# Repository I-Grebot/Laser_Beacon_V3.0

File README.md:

# Laser_Beacon_V3.0
IGrebot's current Beacons system aiming at opponent detection and absolute positioning.

See more on : http://wiki.igrebot.fr/index.php?title=Beacon_V3.0

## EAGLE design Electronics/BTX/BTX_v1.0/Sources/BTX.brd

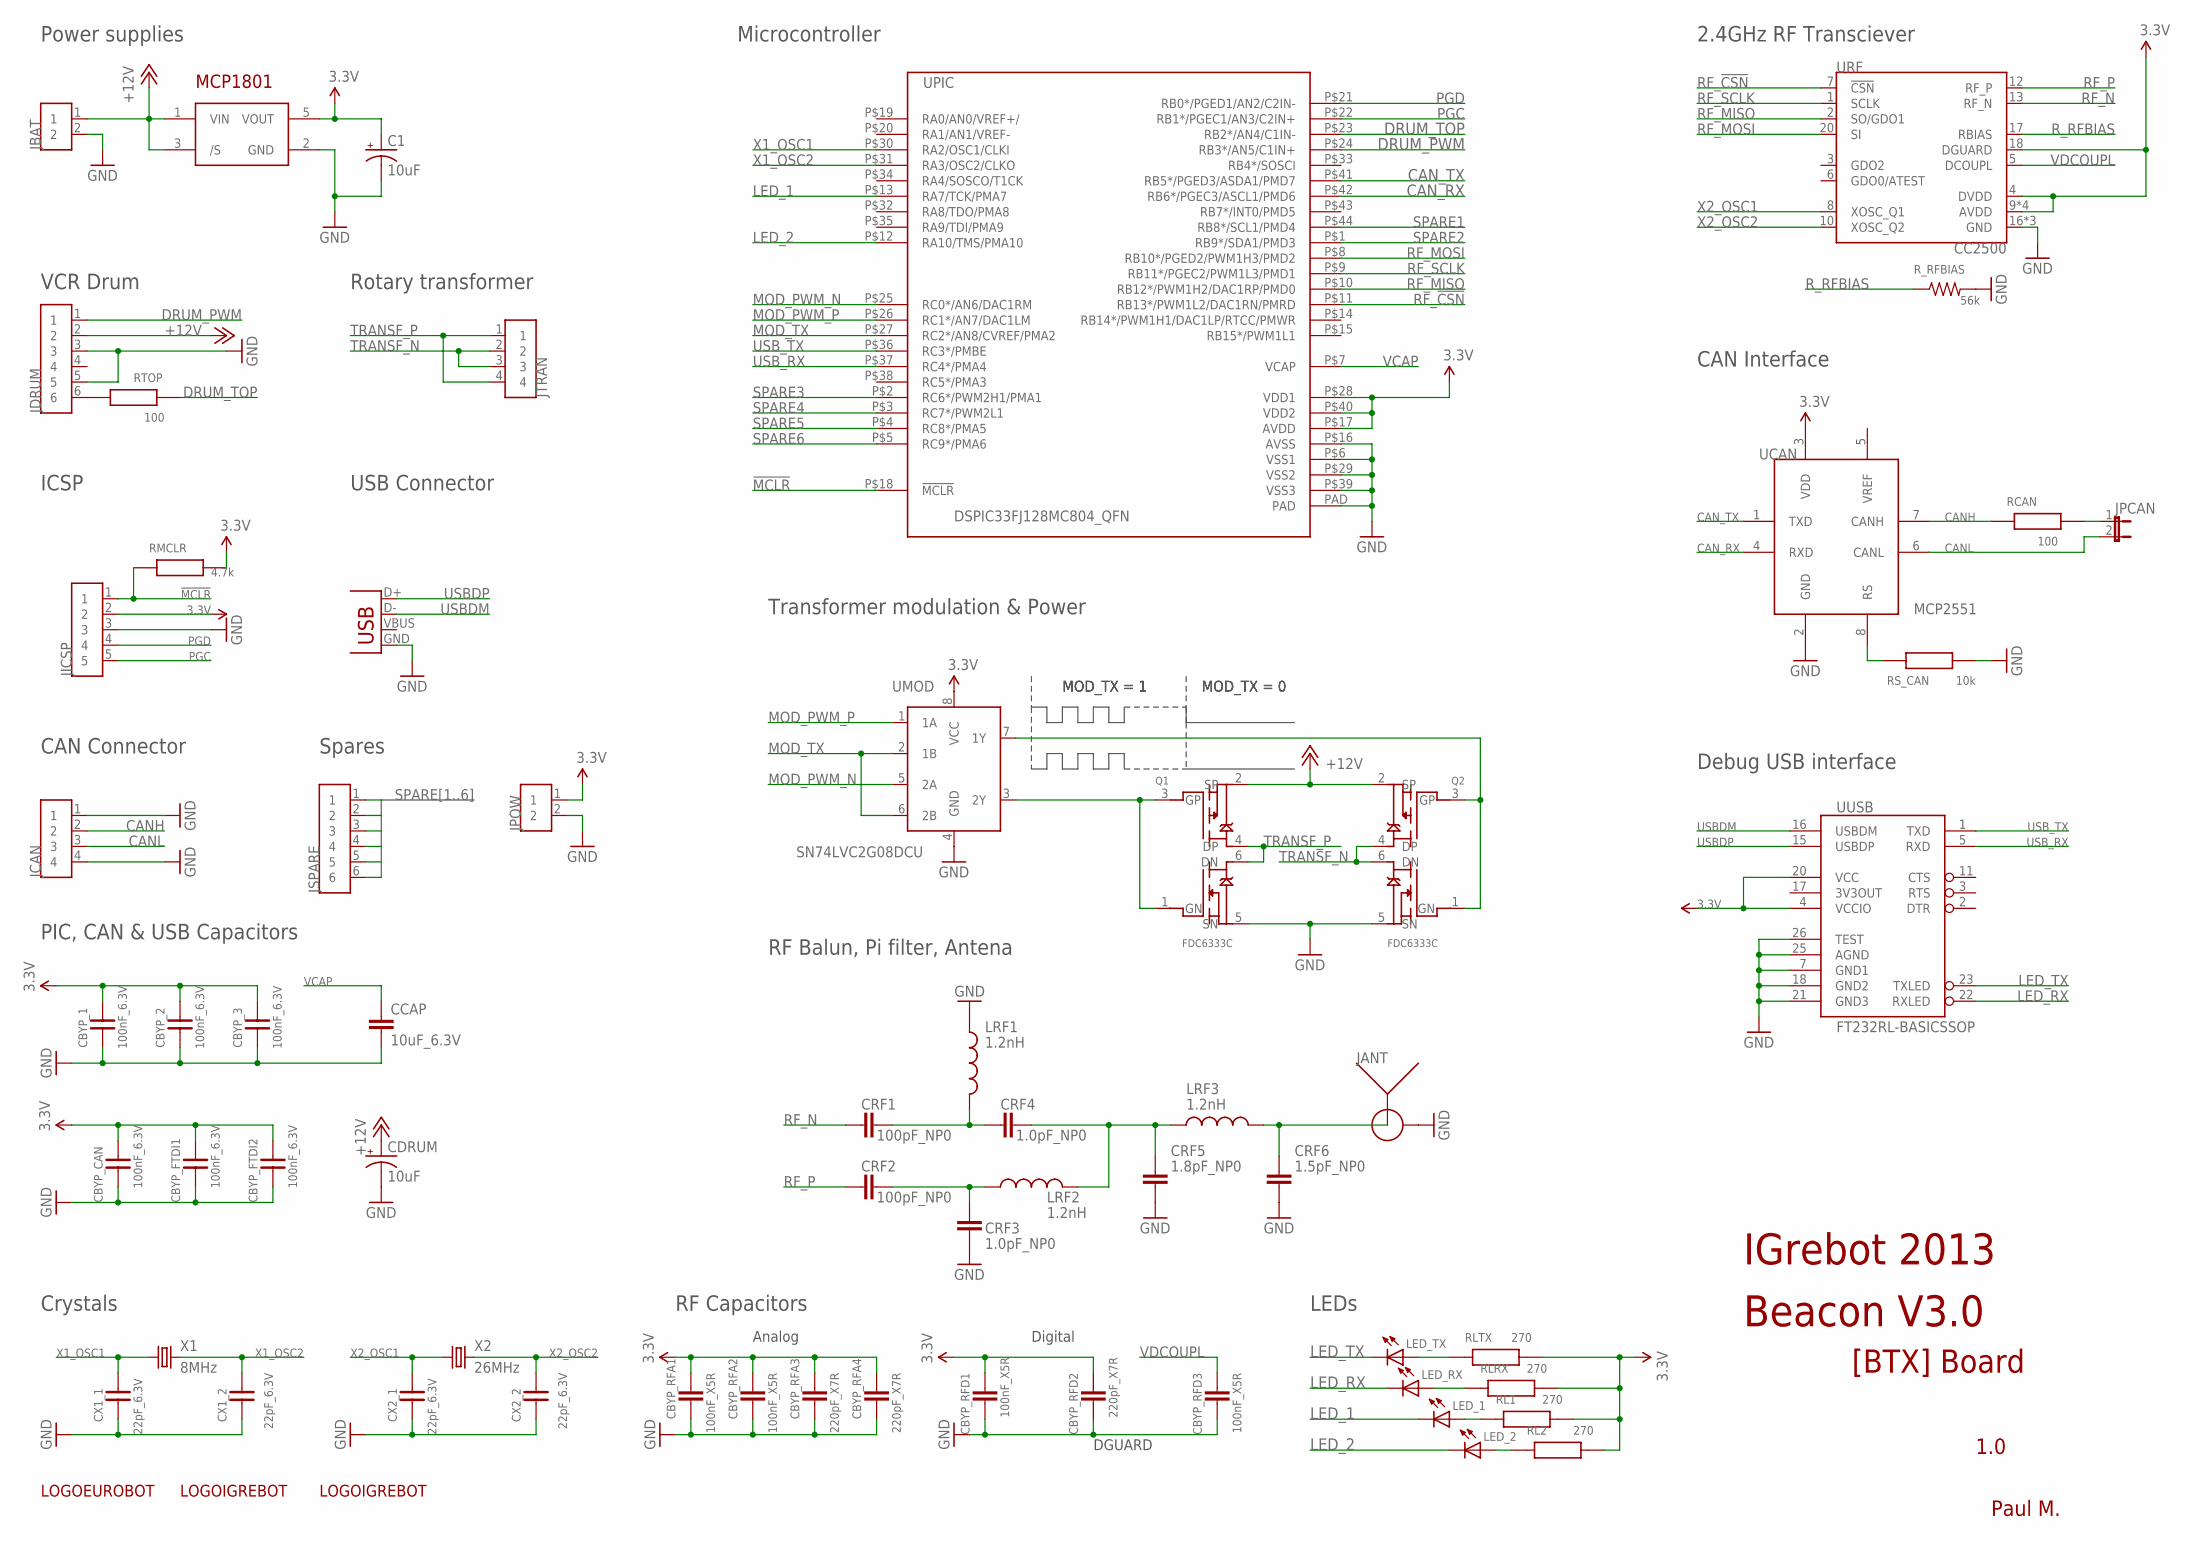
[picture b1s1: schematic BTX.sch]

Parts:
C1: 10uF; PANASONIC_C
CBYP_1, CBYP_2, CBYP_3: 100nF_6.3V; R0603
CBYP_CAN: 100nF_6.3V; R0603
CBYP_FTDI1, CBYP_FTDI2: 100nF_6.3V; R0603
CBYP_RFA1, CBYP_RFA2: 100nF_X5R; 0402-CAP
CBYP_RFA3, CBYP_RFA4: 220pF_X7R; 0402-CAP
CBYP_RFD1, CBYP_RFD3: 100nF_X5R; 0402-CAP
CBYP_RFD2: 220pF_X7R; 0402-CAP
CCAP: 10uF_6.3V; 1206
CDRUM: 10uF; PANASONIC_C
CRF1, CRF2: 100pF_NP0; 0402-CAP
CRF3, CRF4: 1.0pF_NP0; 0402-CAP
CRF5: 1.8pF_NP0; 0402-CAP
CRF6: 1.5pF_NP0; 0402-CAP
CX1_1, CX1_2, CX2_1, CX2_2: 22pF_6.3V; R0603
JANT: ENG_CD_1814400_C1; SMA-PCB-ANGLE
JBAT: MULTICOMP_PA001-2; CON2-5.00
JCAN: SIL4; CON4-2.54
JDRUM: SIL6; CON6-2.54
JICSP: SIL5; CON5-2.54
JPCAN: JUMPER-2PTH_LOCK; 1X02_LOCK
JPOW: SIL2; CON2-2.54
JSPARE: SIL6; CON6-2.54
JTRAN: SIL4; CON4-2.54
JUSB: USBSMD; USB-MINIB
LED_1, LED_2: LED0603; LED-0603
LED_RX: LED0603; LED-0603
LED_TX: LED0603; LED-0603
LRF1, LRF2, LRF3: 1.2nH; C0402
Q1, Q2: FDC6333C; SSOT6
RCAN: 100; R0603
RL1, RL2: 270; R0603
RLRX: 270; R0603
RLTX: 270; R0603
RMCLR: 4.7k; R0603
RS_CAN: 10k; R0603
RTOP: 100; R0603
R_RFBIAS: 56k; 0402-RES
U$3: LOGOEUROBOT; LOGO_EUROBOT_1
U$5, U$9: LOGOIGREBOT; LOGO_IGREBOT
UCAN: MCP2551; SO-08
UMOD: SN74LVC2G08DCU; DCU8
UPIC: DSPIC33FJ128MC804_QFN; QFN44-8X8
UREG: MCP1801; SOT23-5L
URF: CC2500; QFN20-0.5
UUSB: FT232RL-BASICSSOP; SSOP28DB
X1: 8MHz; XTAL_4.9-1.8
X2: 26MHz; XTAL_4.9-1.8

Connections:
3.3V: C1.+, CBYP_1.1, CBYP_2.1, CBYP_3.1, CBYP_CAN.1, CBYP_FTDI1.1, CBYP_FTDI2.1, CBYP_RFA1.2, CBYP_RFA2.2, CBYP_RFA3.2, CBYP_RFA4.2, CBYP_RFD1.2, CBYP_RFD2.2, JICSP.2, JPOW.1, RL1.1, RL2.1, RLRX.1, RLTX.1, RMCLR.1, UCAN.3 (VDD), UMOD.8 (VCC), UPIC.P$17 (AVDD), UPIC.P$28 (VDD1), UPIC.P$40 (VDD2), UREG.5 (VOUT), URF.4 (DVDD), URF.9 (AVDD), URF.11 (AVDD), URF.14 (AVDD), URF.15 (AVDD), URF.18 (DGUARD), UUSB.4 (VCCIO), UUSB.20 (VCC)
!MCLR!: JICSP.1, RMCLR.2, UPIC.P$18 (!MCLR)
+12V: CDRUM.+, JBAT.1, JDRUM.2, Q1.2 (SP), Q2.2 (SP), UREG.1 (VIN), UREG.3 (/S)
CANH: JCAN.2, RCAN.1, UCAN.7 (CANH)
CANL: JCAN.3, JPCAN.2, UCAN.6 (CANL)
CAN_RX: UCAN.4 (RXD), UPIC.P$42 (RB6*/PGEC3/ASCL1/PMD6)
CAN_TX: UCAN.1 (TXD), UPIC.P$41 (RB5*/PGED3/ASDA1/PMD7)
DRUM_PWM: JDRUM.1, UPIC.P$24 (RB3*/AN5/C1IN+)
DRUM_TOP: RTOP.1, UPIC.P$23 (RB2*/AN4/C1IN-)
GND: C1.-, CBYP_1.2, CBYP_2.2, CBYP_3.2, CBYP_CAN.2, CBYP_FTDI1.2, CBYP_FTDI2.2, CBYP_RFA1.1, CBYP_RFA2.1, CBYP_RFA3.1, CBYP_RFA4.1, CBYP_RFD1.1, CBYP_RFD2.1, CBYP_RFD3.1, CCAP.2, CDRUM.-, CRF3.1, CRF5.1, CRF6.1, CX1_1.2, CX1_2.2, CX2_1.2, CX2_2.2, JANT.B1 (B), JANT.B2 (B), JANT.B3 (B), JANT.B4 (B), JBAT.2, JCAN.1, JCAN.4, JDRUM.3, JDRUM.5, JICSP.3, JPOW.2, JUSB.GND, LRF1.1, Q1.5 (SN), Q2.5 (SN), RS_CAN.1, R_RFBIAS.2, UCAN.2 (GND), UMOD.4 (GND), UPIC.P$6 (VSS1), UPIC.P$16 (AVSS), UPIC.P$29 (VSS2), UPIC.P$39 (VSS3), UPIC.PAD, UREG.2 (GND), URF.16 (GND), URF.19 (GND), URF.PAD (GND), UUSB.7 (GND1), UUSB.18 (GND2), UUSB.21 (GND3), UUSB.25 (AGND), UUSB.26 (TEST)
LED_1: LED_1.C, UPIC.P$13 (RA7/TCK/PMA7)
LED_2: LED_2.C, UPIC.P$12 (RA10/TMS/PMA10)
LED_RX: LED_RX.C, UUSB.22 (RXLED)
LED_TX: LED_TX.C, UUSB.23 (TXLED)
MOD_N: Q1.1 (GN), Q1.3 (GP), UMOD.3 (2Y)
MOD_P: Q2.1 (GN), Q2.3 (GP), UMOD.7 (1Y)
MOD_PWM_N: UMOD.5 (2A), UPIC.P$25 (RC0*/AN6/DAC1RM)
MOD_PWM_P: UMOD.1 (1A), UPIC.P$26 (RC1*/AN7/DAC1LM)
MOD_TX: UMOD.2 (1B), UMOD.6 (2B), UPIC.P$27 (RC2*/AN8/CVREF/PMA2)
unnamed: CRF1.2, CRF4.2, LRF1.2
unnamed: LED_TX.A, RLTX.2
unnamed: CRF2.2, CRF3.2, LRF2.1
unnamed: CRF4.1, CRF5.2, LRF2.2, LRF3.1
unnamed: RS_CAN.2, UCAN.8 (RS)
unnamed: JPCAN.1, RCAN.2
unnamed: CRF6.2, JANT.A, LRF3.2
unnamed: LED_RX.A, RLRX.2
unnamed: LED_1.A, RL1.2
unnamed: LED_2.A, RL2.2
PGC: JICSP.5, UPIC.P$22 (RB1*/PGEC1/AN3/C2IN+)
PGD: JICSP.4, UPIC.P$21 (RB0*/PGED1/AN2/C2IN-)
RF_!CSN!: UPIC.P$11 (RB13*/PWM1L2/DAC1RN/PMRD), URF.7 (!CSN!)
RF_MISO: UPIC.P$10 (RB12*/PWM1H2/DAC1RP/PMD0), URF.2 (SO/GDO1)
RF_MOSI: UPIC.P$8 (RB10*/PGED2/PWM1H3/PMD2), URF.20 (SI)
RF_N: CRF1.1, URF.13 (RF_N)
RF_P: CRF2.1, URF.12 (RF_P)
RF_SCLK: UPIC.P$9 (RB11*/PGEC2/PWM1L3/PMD1), URF.1 (SCLK)
RTOP: JDRUM.6, RTOP.2
R_RFBIAS: R_RFBIAS.1, URF.17 (RBIAS)
SPARE1: JSPARE.1, UPIC.P$44 (RB8*/SCL1/PMD4)
SPARE2: JSPARE.2, UPIC.P$1 (RB9*/SDA1/PMD3)
SPARE3: JSPARE.3, UPIC.P$2 (RC6*/PWM2H1/PMA1)
SPARE4: JSPARE.4, UPIC.P$3 (RC7*/PWM2L1)
SPARE5: JSPARE.5, UPIC.P$4 (RC8*/PMA5)
SPARE6: JSPARE.6, UPIC.P$5 (RC9*/PMA6)
TRANSF_N: JTRAN.2, JTRAN.3, Q2.4 (DP), Q2.6 (DN)
TRANSF_P: JTRAN.1, JTRAN.4, Q1.4 (DP), Q1.6 (DN)
USBDM: JUSB.D-, UUSB.16 (USBDM)
USBDP: JUSB.D+, UUSB.15 (USBDP)
USB_RX: UPIC.P$37 (RC4*/PMA4), UUSB.5 (RXD)
USB_TX: UPIC.P$36 (RC3*/PMBE), UUSB.1 (TXD)
VCAP: CCAP.1, UPIC.P$7 (VCAP)
VDCOUPL: CBYP_RFD3.2, URF.5 (DCOUPL)
X1_OSC1: CX1_1.1, UPIC.P$30 (RA2/OSC1/CLKI), X1.P$1 (1)
X1_OSC2: CX1_2.1, UPIC.P$31 (RA3/OSC2/CLKO), X1.P$2 (2)
X2_OSC1: CX2_1.1, URF.8 (XOSC_Q1), X2.P$1 (1)
X2_OSC2: CX2_2.1, URF.10 (XOSC_Q2), X2.P$2 (2)

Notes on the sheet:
Debug USB interface
CAN Interface
LEDs
PIC, CAN & USB Capacitors
USB Connector
Power supplies
ICSP
Rotary transformer
VCR Drum
Transformer modulation & Power
DGUARD
RF Balun, Pi filter, Antena
2.4GHz RF Transciever
Crystals
RF Capacitors
Analog
Digital
CAN Connector
Microcontroller
MOD_TX = 1
MOD_TX = 0
Spares
IGrebot 2013
Beacon V3.0
[BTX] Board
1.0
Paul M.

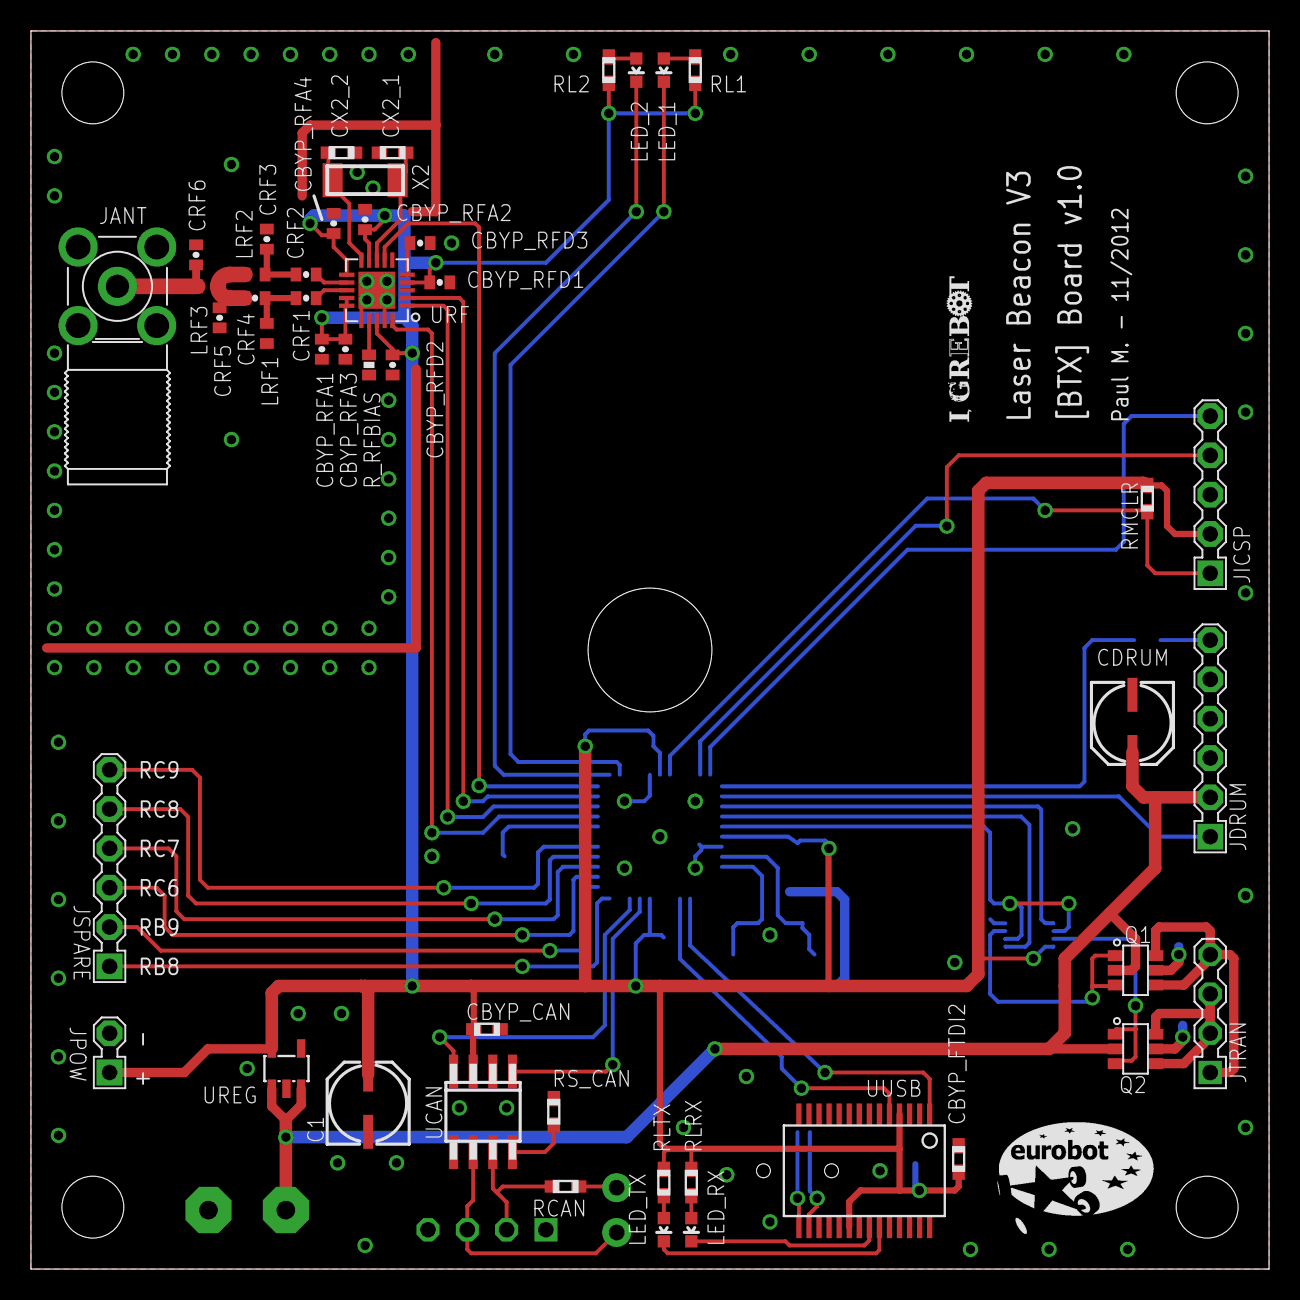
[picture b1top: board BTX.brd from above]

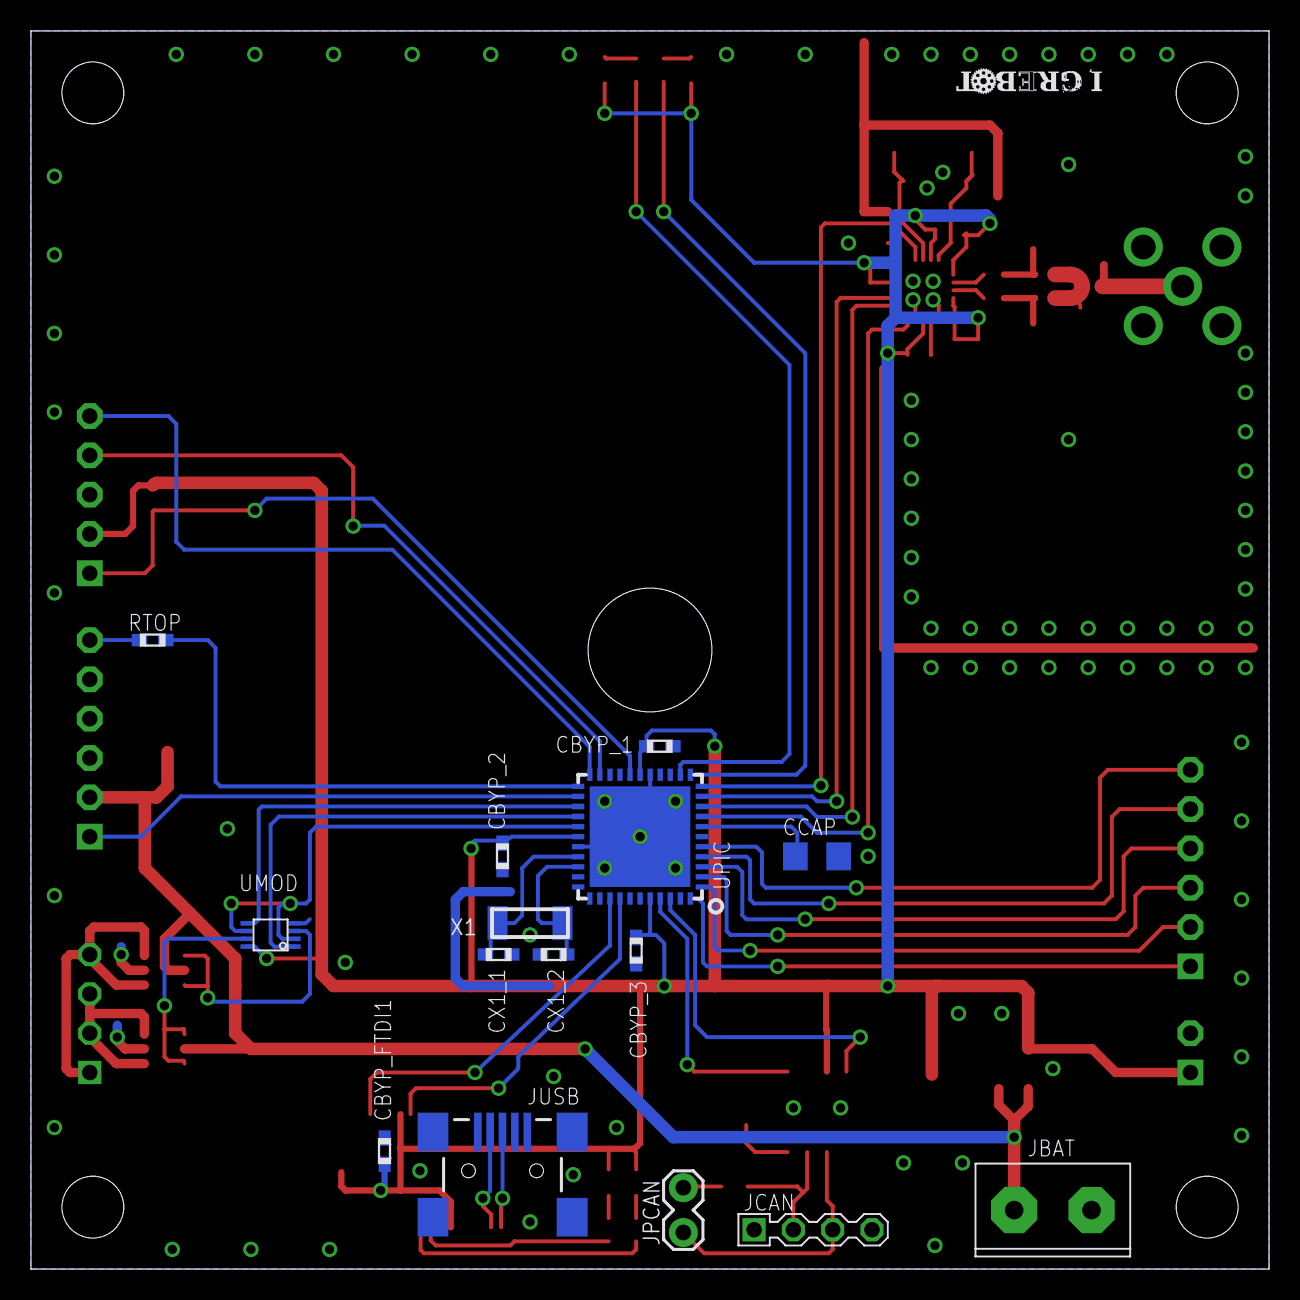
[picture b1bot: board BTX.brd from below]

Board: 2 copper layers, 80.0 x 80.0 mm, 65 parts (16 on the bottom side), 57 nets.

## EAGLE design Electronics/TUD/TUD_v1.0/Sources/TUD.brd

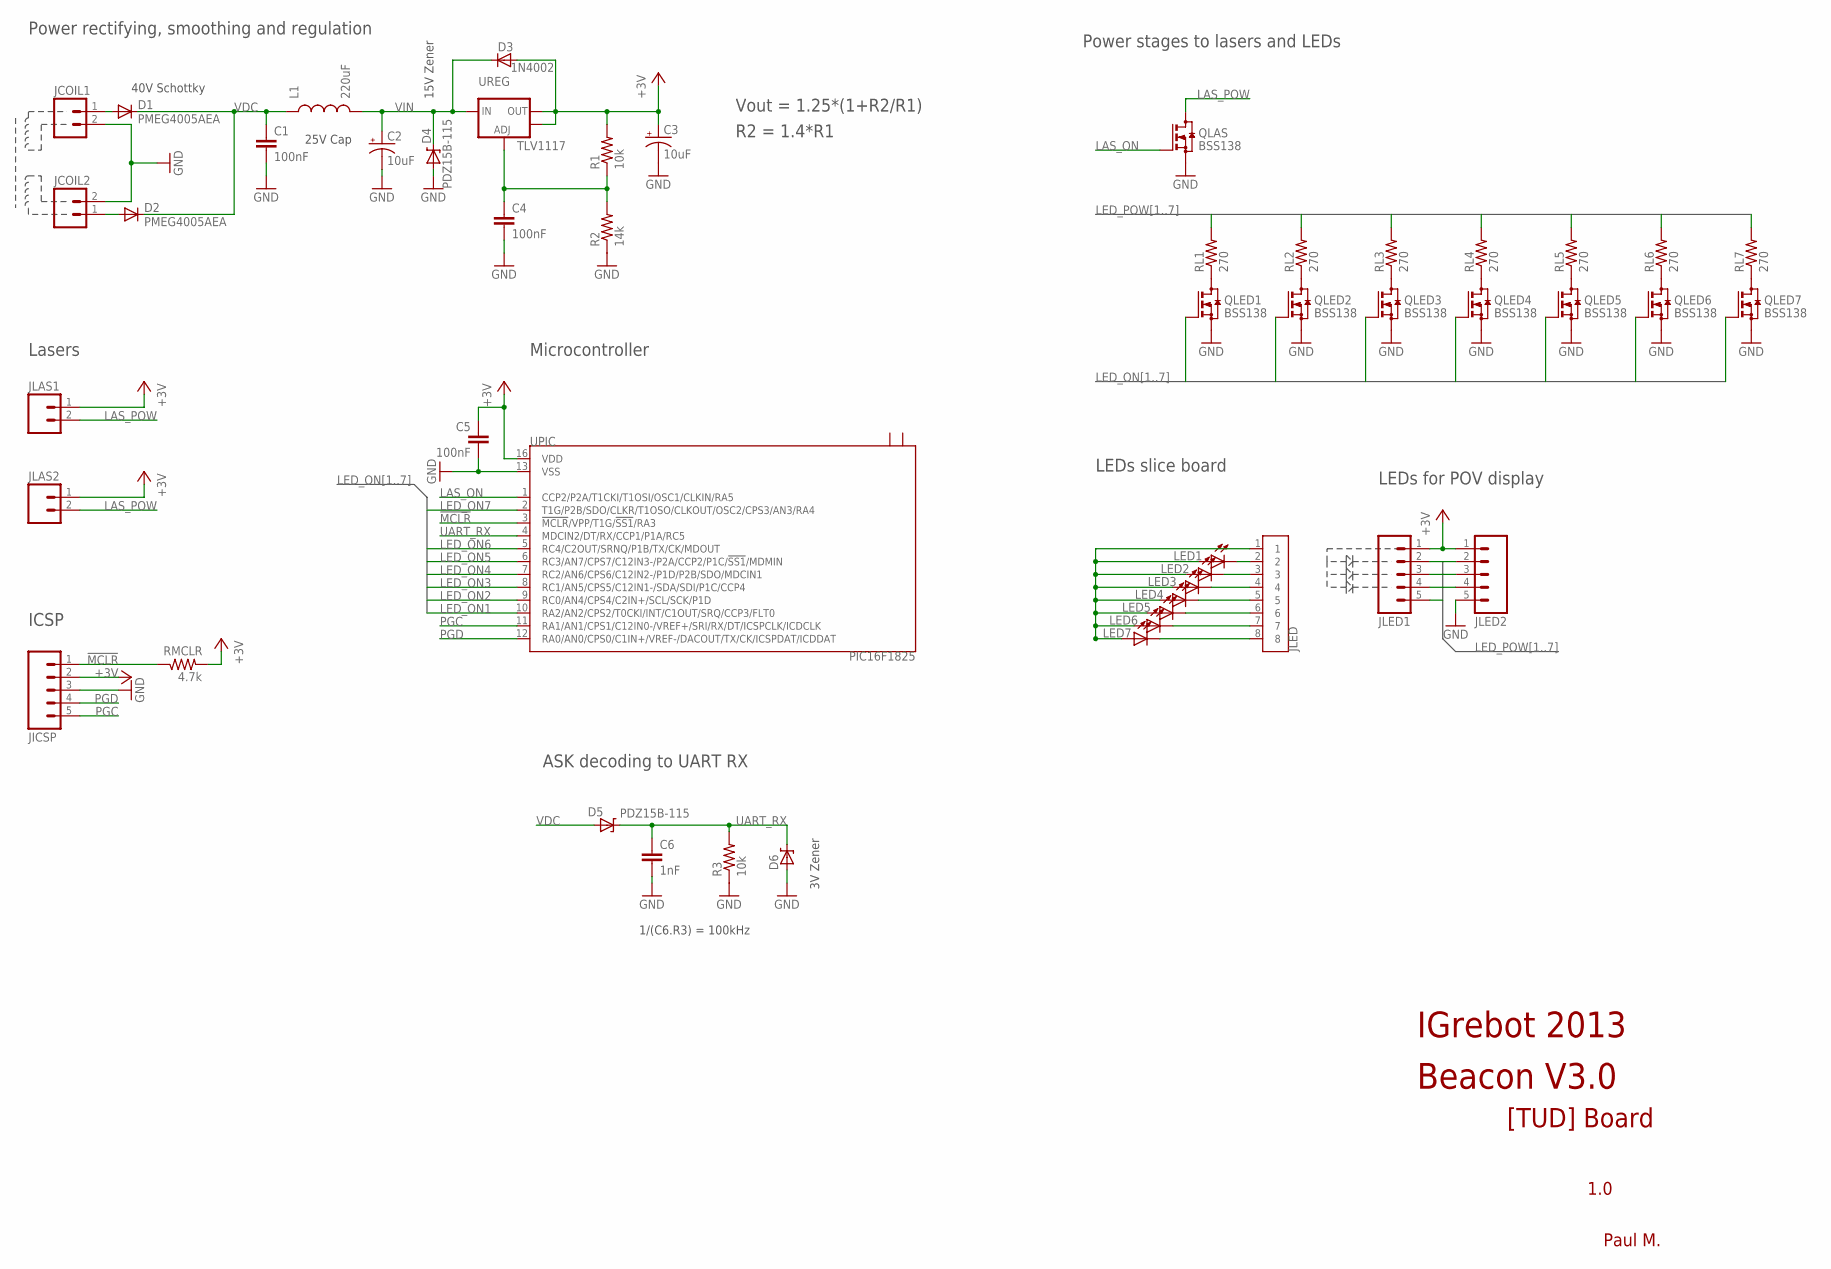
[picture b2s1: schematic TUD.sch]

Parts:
C1, C4, C5: 100nF; 0603-CAP
C2, C3: 10uF; EIA3528
C6: 1nF; 0603-CAP
D1, D2: PMEG4005AEA; SOD-323
D3: 1N4002; SOD-323
D4, D5: PDZ15B-115; SOD-323
D6: DIODE-ZENER-BZT52; SOD-323
JCOIL1, JCOIL2: M02LOCK; 1X02_LOCK
JICSP: M051.27MM; 1X05-1.27MM
JLAS1, JLAS2: M02LOCK; 1X02_LOCK
JLED: CON8_SMD-1; CON8-SMD-1
JLED1, JLED2: M051.27MM; 1X05-1.27MM
L1: 220uF; L-5X5
LED1, LED2, LED3, LED4, LED5, LED6, LED7: LED0603; LED-0603
QLAS: BSS138; SOT23
QLED1, QLED2, QLED3, QLED4, QLED5, QLED6, QLED7: BSS138; SOT23
R1, R3: 10k; 0603-RES
R2: 14k; 0603-RES
RL1, RL2, RL3, RL4, RL5, RL6, RL7: 270; 0603-RES
RMCLR: 4.7k; 0603-RES
UPIC: PIC16F1825; QFN16-0.65
UREG: TLV1117; SOT223

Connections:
!MCLR!: JICSP.1, RMCLR.1, UPIC.3 (!MCLR!/VPP/T1G/!SS1!/RA3)
+3V3: C3.A (+), C5.1, D3.2 (A), JICSP.2, JLAS1.1, JLAS2.1, JLED1.1, JLED2.1, R1.2, RMCLR.2, UPIC.16 (VDD), UREG.2 (OUT), UREG.4 (OUT)
GND: C1.2, C2.C (-), C3.C (-), C4.2, C5.2, C6.2, D4.2 (A), D6.2 (A), JCOIL1.2, JCOIL2.2, JICSP.3, JLED2.5, QLAS.2 (S), QLED1.2 (S), QLED2.2 (S), QLED3.2 (S), QLED4.2 (S), QLED5.2 (S), QLED6.2 (S), QLED7.2 (S), R2.1, R3.1, UPIC.13 (VSS)
LAS_ON: QLAS.1 (G), UPIC.1 (CCP2/P2A/T1CKI/T1OSI/OSC1/CLKIN/RA5)
LAS_POW: JLAS1.2, JLAS2.2, QLAS.3 (D)
LED_ON1: QLED1.1 (G), UPIC.10 (RA2/AN2/CPS2/T0CKI/INT/C1OUT/SRQ/CCP3/F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)
LED_ON2: QLED2.1 (G), UPIC.9 (RC0/AN4/CPS4/C2IN+/SCL/SCK/P1D)
LED_ON3: QLED3.1 (G), UPIC.8 (RC1/AN5/CPS5/C12IN1-/SDA/SDI/P1C/CCP4)
LED_ON4: QLED4.1 (G), UPIC.7 (RC2/AN6/CPS6/C12IN2-/P1D/P2B/SDO/MDCIN1)
LED_ON5: QLED5.1 (G), UPIC.6 (RC3/AN7/CPS7/C12IN3-/P2A/CCP2/P1C/!SS1!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)
LED_ON6: QLED6.1 (G), UPIC.5 (RC4/C2OUT/SRNQ/P1B/TX/CK/MDOUT)
LED_ON7: QLED7.1 (G), UPIC.2 (T1G/P2B/SDO/CLKR/T1OSO/CLKOUT/OSC2/CPS3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)
LED_POW1: JLED1.2, RL1.2
LED_POW2: JLED1.3, RL2.2
LED_POW3: JLED1.4, RL3.2
LED_POW4: JLED1.5, RL4.2
LED_POW5: JLED2.2, RL5.2
LED_POW6: JLED2.3, RL6.2
LED_POW7: JLED2.4, RL7.2
unnamed: JLED.2, LED1.C
unnamed: D1.2 (A), JCOIL1.1
unnamed: D2.2 (A), JCOIL2.1
unnamed: JLED.3, LED2.C
unnamed: QLED1.3 (D), RL1.1
unnamed: C4.1, R1.1, R2.2, UREG.1 (ADJ)
unnamed: QLED2.3 (D), RL2.1
unnamed: QLED3.3 (D), RL3.1
unnamed: QLED4.3 (D), RL4.1
unnamed: QLED5.3 (D), RL5.1
unnamed: QLED6.3 (D), RL6.1
unnamed: QLED7.3 (D), RL7.1
unnamed: JLED.4, LED3.C
unnamed: JLED.5, LED4.C
unnamed: JLED.6, LED5.C
unnamed: JLED.7, LED6.C
unnamed: JLED.8, LED7.C
unnamed: JLED.1, LED1.A, LED2.A, LED3.A, LED4.A, LED5.A, LED6.A, LED7.A
PGC: JICSP.5, UPIC.11 (RA1/AN1/CPS1/C12IN0-/VREF+/SRI/RX/DT/IC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)
PGD: JICSP.4, UPIC.12 (RA0/AN0/CPS0/C1IN+/VREF-/DACOUT/TX/CK/I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)
UART_RX: C6.1, D5.1 (C), D6.1 (C), R3.2, UPIC.4 (MDCIN2/DT/RX/CCP1/P1A/RC5)
VDC: C1.1, D1.1 (C), D2.1 (C), D5.2 (A), L1.1
VIN: C2.A (+), D3.1 (C), D4.1 (C), L1.2, UREG.3 (IN)

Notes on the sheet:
1.0
Paul M.
Vout = 1.25*(1+R2/R1)
R2 = 1.4*R1
40V Schottky
15V Zener
25V Cap
3V Zener
1/(C6.R3) = 100kHz
IGrebot 2013
Beacon V3.0
[TUD] Board
Power rectifying, smoothing and regulation
Power stages to lasers and LEDs
Microcontroller
ASK decoding to UART RX
LEDs slice board
LEDs for POV display
Lasers
ICSP

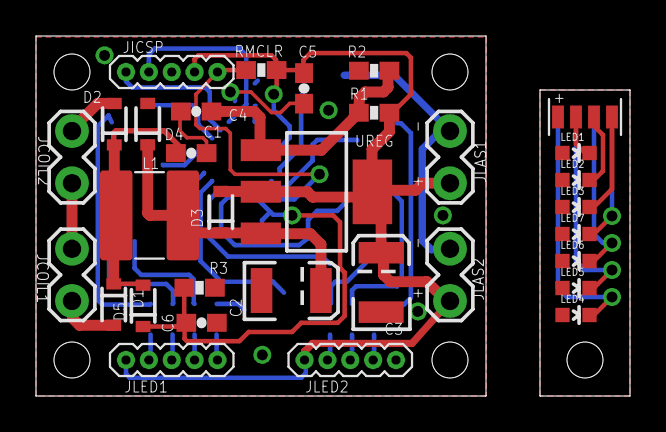
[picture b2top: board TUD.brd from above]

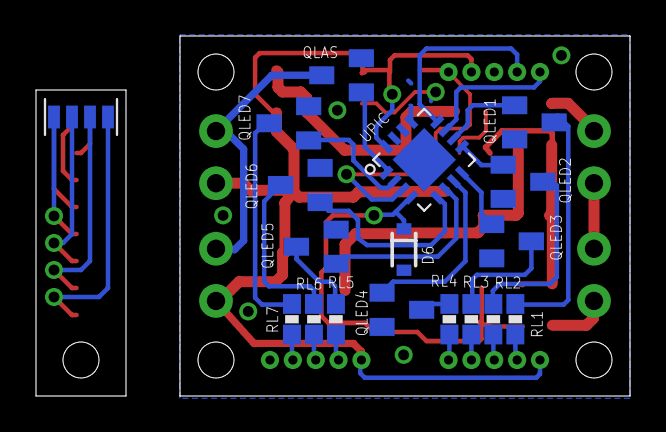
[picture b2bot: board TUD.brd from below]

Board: 2 copper layers, 33.0 x 20.0 mm, 49 parts (17 on the bottom side), 42 nets.

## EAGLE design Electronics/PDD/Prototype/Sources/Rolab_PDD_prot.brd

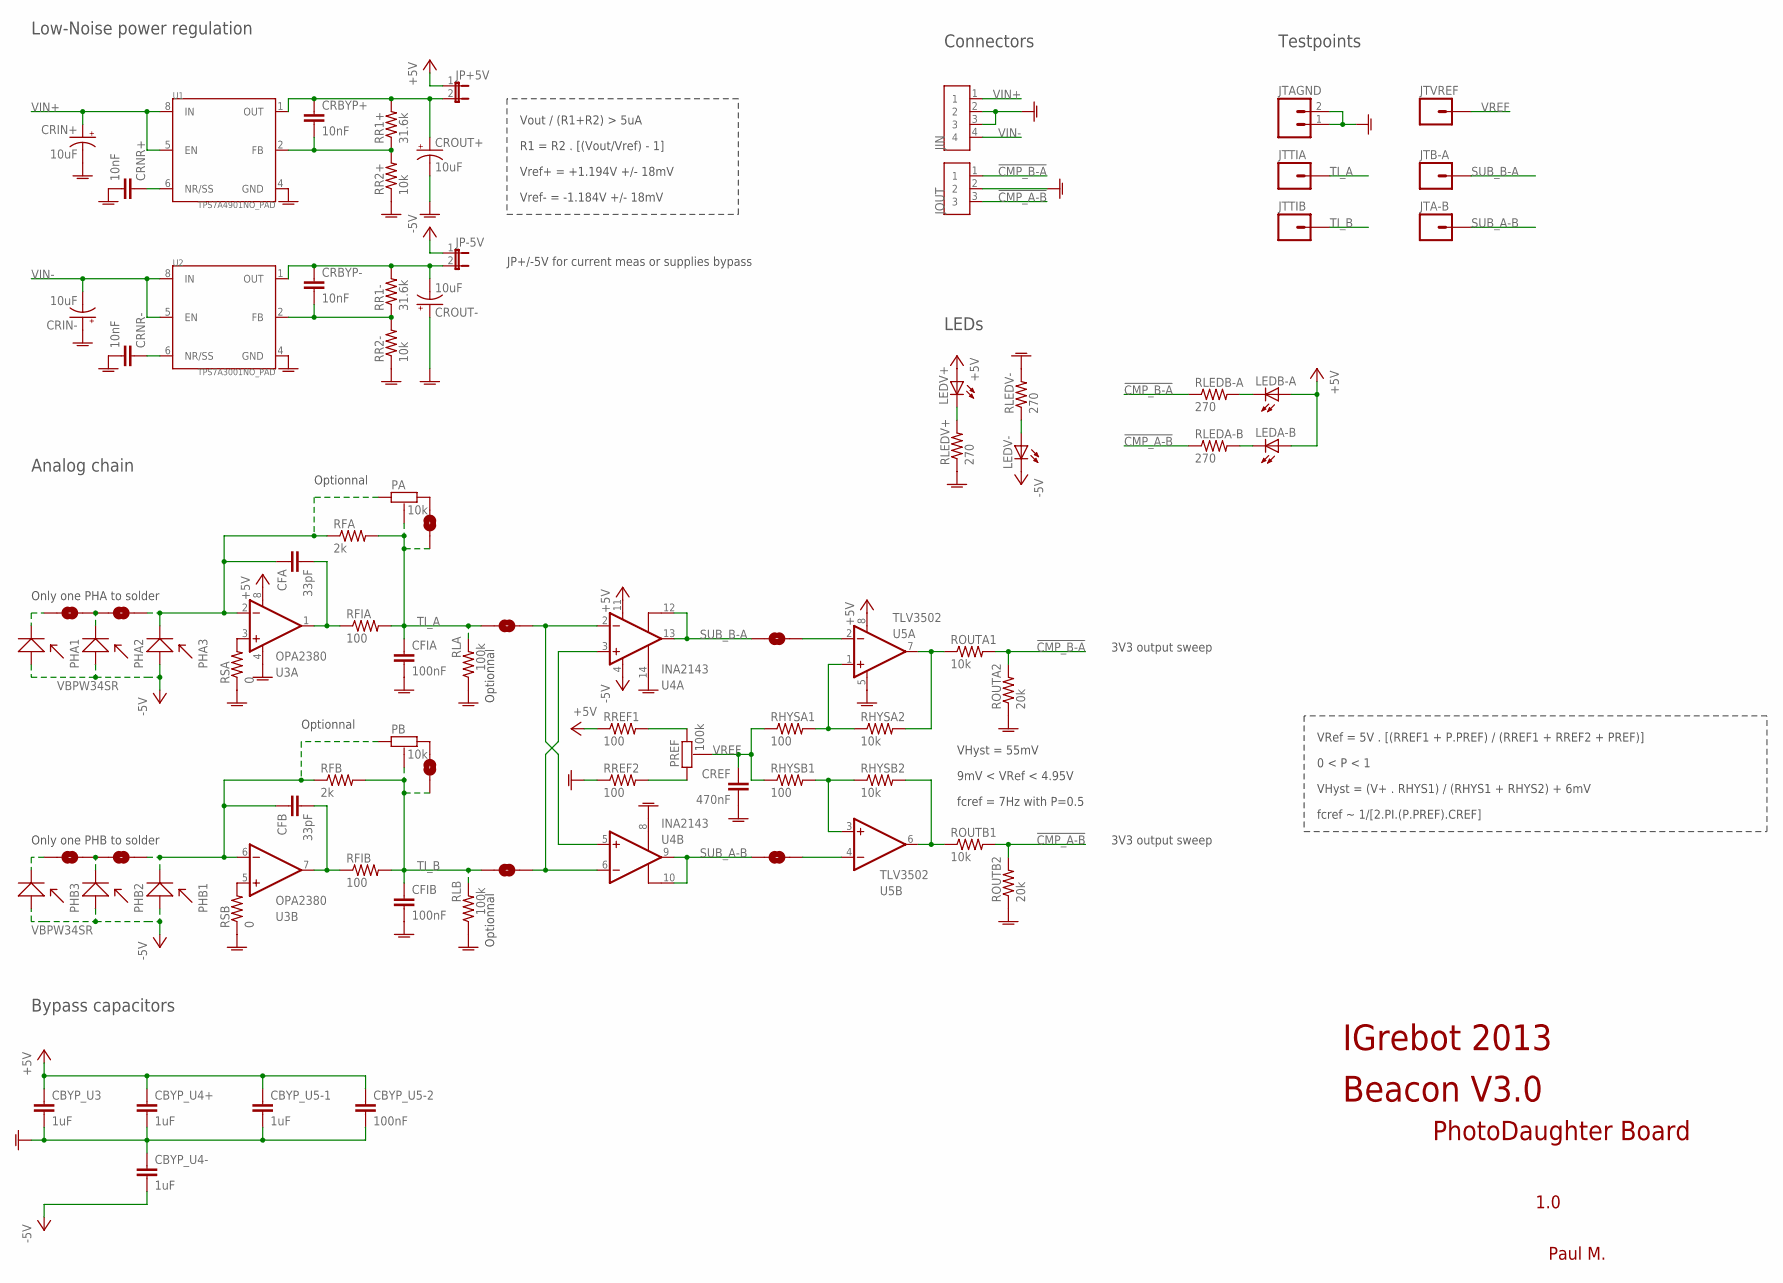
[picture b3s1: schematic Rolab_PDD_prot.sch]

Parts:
CBYP_U3, CBYP_U4+, CBYP_U4-, CBYP_U5-1: 1uF; 0603-CAP
CBYP_U5-2: 100nF; 0603-CAP
CFA: 33pF; 0603-CAP
CFB: 33pF; 0603-CAP
CFIA: 100nF; 0603-CAP
CFIB: 100nF; 0603-CAP
CRBYP+: 10nF; 0603-CAP
CRBYP-: 10nF; 0603-CAP
CREF: 470nF; 0603-CAP
CRIN+: 10uF; EIA3528-KIT
CRIN-: 10uF; EIA3528-KIT
CRNR+: 10nF; 0603-CAP
CRNR-: 10nF; 0603-CAP
CROUT+: 10uF; EIA3528-KIT
CROUT-: 10uF; EIA3528-KIT
JIN: SIL4; CON4-2.54
JOUT: SIL3; CON3-2.54
JP+5V: JUMPER-2PTH_LOCK; 1X02_LOCK
JP-5V: JUMPER-2PTH_LOCK; 1X02_LOCK
JTA-B: M01PTH; 1X01
JTAGND: M02LOCK; 1X02_LOCK
JTB-A: M01PTH; 1X01
JTTIA: M01PTH; 1X01
JTTIB: M01PTH; 1X01
JTVREF: M01PTH; 1X01
LEDA-B: LED0603; LED-0603
LEDB-A: LED0603; LED-0603
LEDV+: LED0603; LED-0603
LEDV-: LED0603; LED-0603
PA: 10k; TRIM-PVZ2A
PB: 10k; TRIM-PVZ2A
PHA1, PHA2, PHA3: VBPW34SR
PHB1, PHB2, PHB3: VBPW34SR
PREF: 100k; TRIM-PVZ2A
RFA: 2k; 0603-RES
RFB: 2k; 0603-RES
RFIA: 100; 0603-RES
RFIB: 100; 0603-RES
RHYSA1: 100; 0603-RES
RHYSA2: 10k; 0603-RES
RHYSB1: 100; 0603-RES
RHYSB2: 10k; 0603-RES
RLA: 100k; 0603-RES
RLB: 100k; 0603-RES
RLEDA-B: 270; 0603-RES
RLEDB-A: 270; 0603-RES
RLEDV+: 270; 0603-RES
RLEDV-: 270; 0603-RES
ROUTA1: 10k; 0603-RES
ROUTA2: 20k; 0603-RES
ROUTB1: 10k; 0603-RES
ROUTB2: 20k; 0603-RES
RR1+, RR1-: 31.6k; 0603-RES
RR2+, RR2-: 10k; 0603-RES
RREF1, RREF2: 100; 0603-RES
RSA: 0; 0603-RES
RSB: 0; 0603-RES
SJ1, SJ2, SJ3, SJ4, SJ5, SJ6, SJ7, SJ8, SJ9, SJ11: SOLDERJUMPERNC; SJ_2S
U1: TPS7A4901NO_PAD; MSOP8
U2: TPS7A3001NO_PAD; MSOP8
U3: OPA2380; MSOP8
U4: INA2143; SOIC14
U5: TLV3502; SOIC8

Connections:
!CMP_A-B!: JOUT.3, RLEDA-B.1, ROUTB1.2, ROUTB2.2
!CMP_B-A!: JOUT.1, RLEDB-A.1, ROUTA1.2, ROUTA2.2
+5V: CBYP_U3.1, CBYP_U4+.1, CBYP_U5-1.1, CBYP_U5-2.1, JP+5V.1, LEDA-B.A, LEDB-A.A, LEDV+.A, RREF1.1, U3.8 (V+), U4.11 (V+), U5.8 (V+)
-5V: CBYP_U4-.2, JP-5V.1, LEDV-.C, PHA1.A, PHA2.A, PHA3.A, PHB1.A, PHB2.A, PHB3.A, U4.4 (V-)
AGND: CBYP_U3.2, CBYP_U4+.2, CBYP_U4-.1, CBYP_U5-1.2, CBYP_U5-2.2, CFIA.2, CFIB.2, CREF.2, CRIN+.C (-), CRIN-.A (+), CRNR+.2, CRNR-.2, CROUT+.C (-), CROUT-.A (+), JIN.2, JIN.3, JOUT.2, JTAGND.1, JTAGND.2, RLA.1, RLB.1, RLEDV+.1, RLEDV-.2, ROUTA2.1, ROUTB2.1, RR2+.1, RR2-.1, RREF2.1, RSA.1, RSB.1, U1.4 (GND), U2.4 (GND), U3.4 (V-), U4.8 (REF), U4.14 (REF), U5.5 (V-)
unnamed: CRNR+.1, U1.6 (NR/SS)
unnamed: CRBYP-.2, RR1-.1, RR2-.2, U2.2 (FB)
unnamed: CFA.2, RFIA.1, U3.1 (OUT)
unnamed: CRNR-.1, U2.6 (NR/SS)
unnamed: CFA.1, PA.3 (C), PHA3.K, RFA.1, SJ7.2, U3.2 (-IN)
unnamed: CFB.2, RFIB.1, U3.7 (OUT)
unnamed: CRBYP+.2, RR1+.1, RR2+.2, U1.2 (FB)
unnamed: CFB.1, PB.3 (C), PHB1.K, RFB.1, SJ5.2, U3.6 (-IN)
unnamed: SJ2.2, U4.3 (+IN), U4.6 (-IN)
unnamed: RHYSA2.2, ROUTA1.1, U5.7 (OUT)
unnamed: SJ1.2, U4.2 (-IN), U4.5 (+IN)
unnamed: SJ3.2, U5.2 (-IN)
unnamed: SJ4.2, U5.4 (-IN)
unnamed: RHYSA1.2, RHYSA2.1, U5.1 (+IN)
unnamed: RHYSB1.2, RHYSB2.1, U5.3 (+IN)
unnamed: RHYSB2.2, ROUTB1.1, U5.6 (OUT)
unnamed: PREF.1 (A), RREF1.2
unnamed: PREF.3 (C), RREF2.2
unnamed: LEDV+.C, RLEDV+.2
unnamed: LEDV-.A, RLEDV-.1
unnamed: LEDB-A.C, RLEDB-A.2
unnamed: LEDA-B.C, RLEDA-B.2
unnamed: RSA.2, U3.3 (+IN)
unnamed: RSB.2, U3.5 (+IN)
unnamed: PA.1 (A), SJ8.2
unnamed: PHB2.K, SJ5.1, SJ9.2
unnamed: CRBYP+.1, CROUT+.A (+), JP+5V.2, RR1+.2, U1.1 (OUT)
unnamed: PHA2.K, SJ7.1, SJ11.2
unnamed: CRBYP-.1, CROUT-.C (-), JP-5V.2, RR1-.2, U2.1 (OUT)
unnamed: PHA1.K, SJ11.1
unnamed: PHB3.K, SJ9.1
unnamed: PB.1 (A), SJ6.2
SUB_A-B: JTA-B.1, SJ4.1, U4.9 (OUT), U4.10 (SENSE)
SUB_B-A: JTB-A.1, SJ3.1, U4.12 (SENSE), U4.13 (OUT)
TI_A: CFIA.1, JTTIA.1, PA.2 (B), RFA.2, RFIA.2, RLA.2, SJ1.1, SJ8.1
TI_B: CFIB.1, JTTIB.1, PB.2 (B), RFB.2, RFIB.2, RLB.2, SJ2.1, SJ6.1
VIN+: CRIN+.A (+), JIN.1, U1.5 (EN), U1.8 (IN)
VIN-: CRIN-.C (-), JIN.4, U2.5 (EN), U2.8 (IN)
VREF: CREF.1, JTVREF.1, PREF.2 (B), RHYSA1.1, RHYSB1.1

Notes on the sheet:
Vout / (R1+R2) > 5uA
R1 = R2 . [(Vout/Vref) - 1]
Vref+ = +1.194V +/- 18mV
Vref- = -1.184V +/- 18mV
Only one PHA to solder
Only one PHB to solder
VHyst = (V+ . RHYS1) / (RHYS1 + RHYS2) + 6mV
Optionnal
VRef = 5V . [(RREF1 + P.PREF) / (RREF1 + RREF2 + PREF)]
0 < P < 1
3V3 output sweep
VHyst = 55mV
Low-Noise power regulation
Analog chain
Connectors
Testpoints
Bypass capacitors
1.0
Paul M.
9mV < VRef < 4.95V
IGrebot 2013
Beacon V3.0
LEDs
PhotoDaughter Board
JP+/-5V for current meas or supplies bypass
fcref ~ 1/[2.PI.(P.PREF).CREF]
fcref = 7Hz with P=0.5

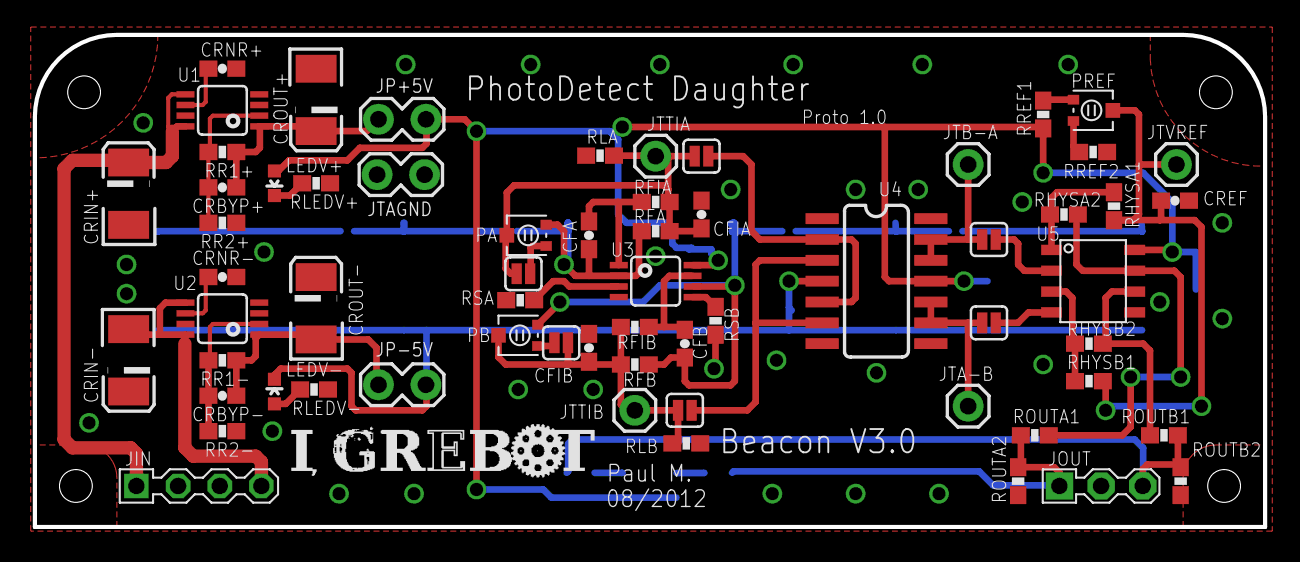
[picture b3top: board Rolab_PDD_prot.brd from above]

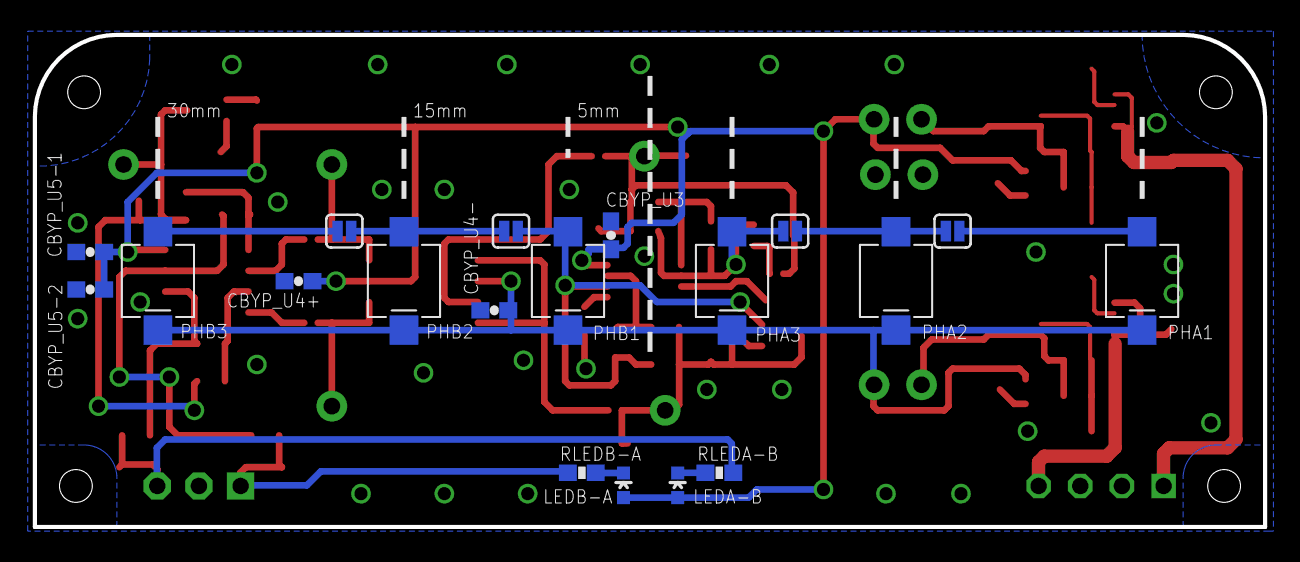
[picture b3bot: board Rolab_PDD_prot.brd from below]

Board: 2 copper layers, 75.0 x 30.0 mm, 82 parts (19 on the bottom side), 44 nets.

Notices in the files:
parts and their libraries:
SparkFun-Passives: Licensing: CC v3.0 Share-Alike You are welcome to use this library for commercial purposes.
